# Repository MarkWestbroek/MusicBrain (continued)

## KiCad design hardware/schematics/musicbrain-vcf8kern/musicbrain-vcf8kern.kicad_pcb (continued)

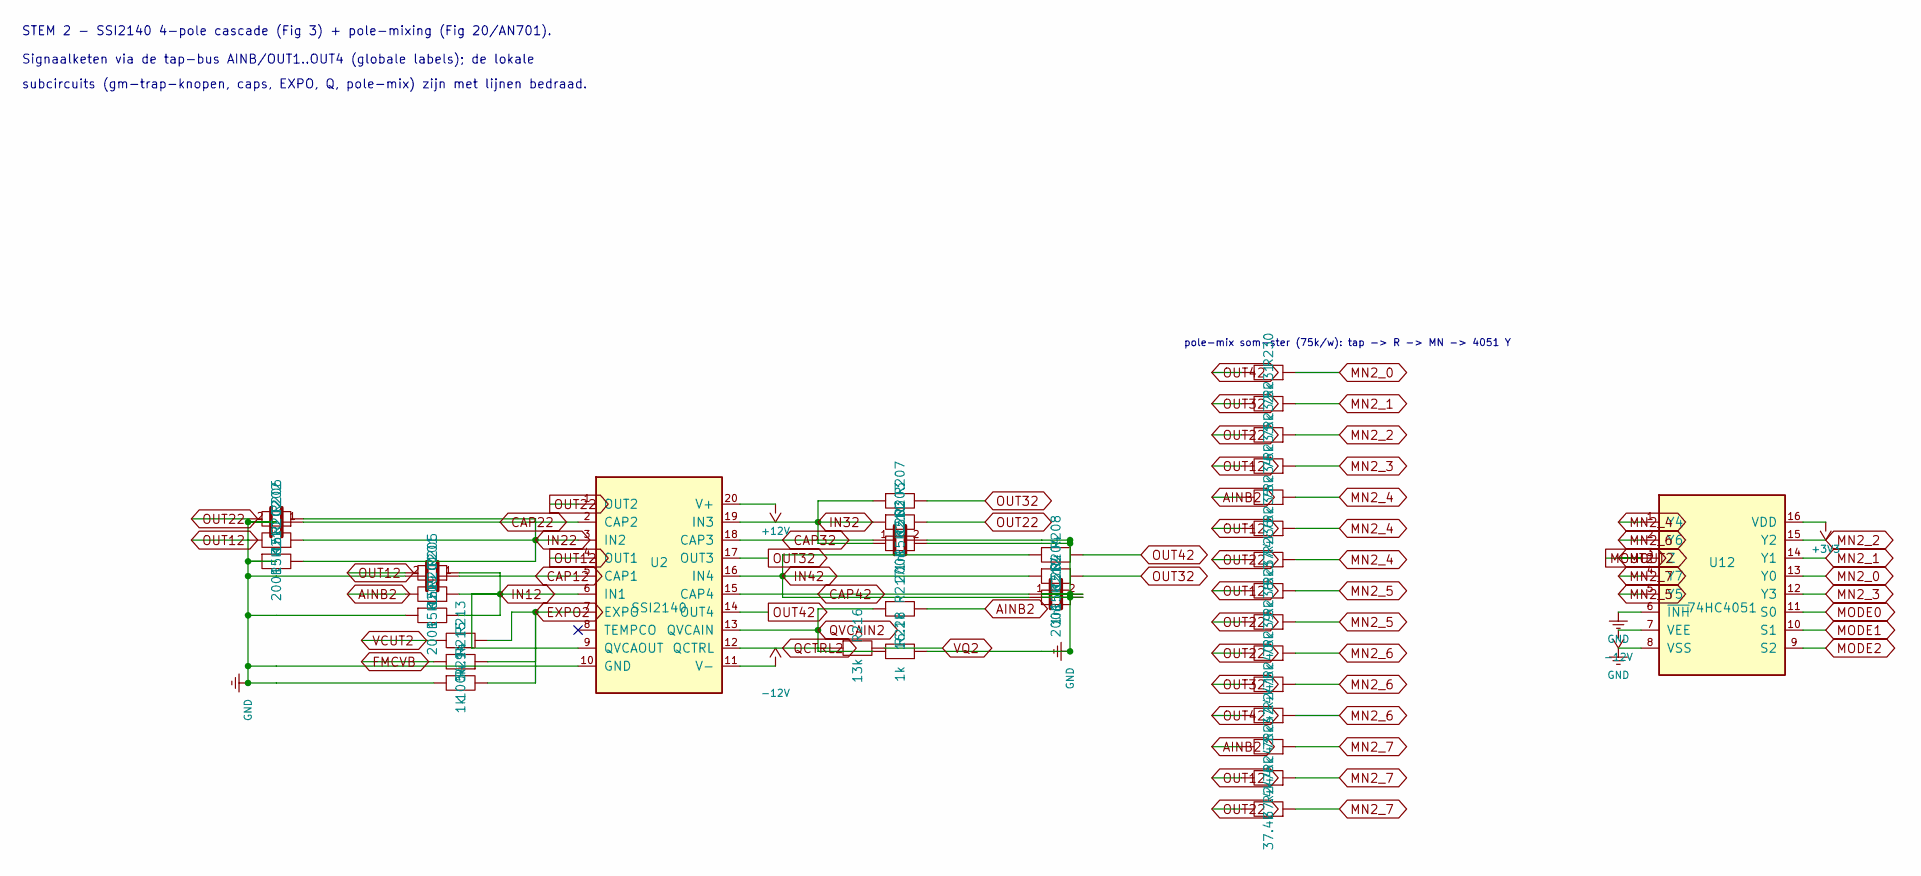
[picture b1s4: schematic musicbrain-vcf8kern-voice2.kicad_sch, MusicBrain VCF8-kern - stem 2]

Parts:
C201, C202, C203, C204: 1n; C_0603_1608Metric
R201, R202, R203, R204, R205, R206, R207, R208: 15k; R_0603_1608Metric
R209, R210, R211, R212: 200R; R_0603_1608Metric
R213: 54.9k; R_0603_1608Metric
R214, R218: 1k; R_0603_1608Metric
R215: 100k; R_0603_1608Metric
R216: 13k; R_0603_1608Metric
R217: 16.2k; R_0603_1608Metric
R230, R231, R232, R233, R234, R236, R237, R238, R239, R241, R242: 75k; R_0603_1608Metric
R235, R240, R243, R244: 37.4k; R_0603_1608Metric
U2: SSI2140; SSOP-20_3.9x8.7mm_P0.635mm
U12: 74HC4051; TSSOP-16_4.4x5mm_P0.65mm

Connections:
+3V3: U12.16 (VDD); also elsewhere on the board
+12V: U2.20 (V+); also elsewhere on the board
-12V: U2.11 (V-), U12.7 (VEE); also elsewhere on the board
AINB2: R201.1, R217.1, R234.1, R242.1; also elsewhere on the board
CAP12: C201.1, U2.5 (CAP1)
CAP22: C202.1, U2.2 (CAP2)
CAP32: C203.1, U2.18 (CAP3)
CAP42: C204.1, U2.15 (CAP4)
EXPO2: R213.2, R214.1, R215.2, U2.7 (EXPO)
FMCVB: R215.1; also elsewhere on the board
GND: C201.2, C202.2, C203.2, C204.2, R209.2, R210.2, R211.2, R212.2, R214.2, R218.2, U2.10 (GND), U12.6 (~INH), U12.8 (VSS); also elsewhere on the board
IN12: R201.2, R205.2, R209.1, U2.6 (IN1), U2.9 (QVCAOUT)
IN22: R202.2, R206.2, R210.1, U2.3 (IN2)
IN32: R203.2, R207.2, R211.1, U2.19 (IN3)
IN42: R204.2, R208.2, R212.1, U2.16 (IN4)
MN2_0: R230.2, U12.13 (Y0)
MN2_1: R231.2, U12.14 (Y1)
MN2_2: R232.2, U12.15 (Y2)
MN2_3: R233.2, U12.12 (Y3)
MN2_4: R234.2, R235.2, R236.2, U12.1 (Y4)
MN2_5: R237.2, R238.2, U12.5 (Y5)
MN2_6: R239.2, R240.2, R241.2, U12.2 (Y6)
MN2_7: R242.2, R243.2, R244.2, U12.4 (Y7)
MODE0: U12.11 (S0); also elsewhere on the board
MODE1: U12.10 (S1); also elsewhere on the board
MODE2: U12.9 (S2); also elsewhere on the board
MOUT2: U12.3 (Z); also elsewhere on the board
OUT12: R202.1, R205.1, R233.1, R235.1, R237.1, R243.1, U2.4 (OUT1)
OUT22: R203.1, R206.1, R232.1, R236.1, R238.1, R239.1, R244.1, U2.1 (OUT2)
OUT32: R204.1, R207.1, R231.1, R240.1, U2.17 (OUT3)
OUT42: R208.1, R230.1, R241.1, U2.14 (OUT4); also elsewhere on the board
QCTRL2: R216.2, U2.12 (QCTRL)
QVCAIN2: R217.2, R218.1, U2.13 (QVCAIN)
VCUT2: R213.1; also elsewhere on the board
VQ2: R216.1; also elsewhere on the board

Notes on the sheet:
pole-mix som-ster (75k/w): tap -> R -> MN -> 4051 Y
STEM 2 - SSI2140 4-pole cascade (Fig 3) + pole-mixing (Fig 20/AN701).
Signaalketen via de tap-bus AINB/OUT1..OUT4 (globale labels); de lokale
subcircuits (gm-trap-knopen, caps, EXPO, Q, pole-mix) zijn met lijnen bedraad.

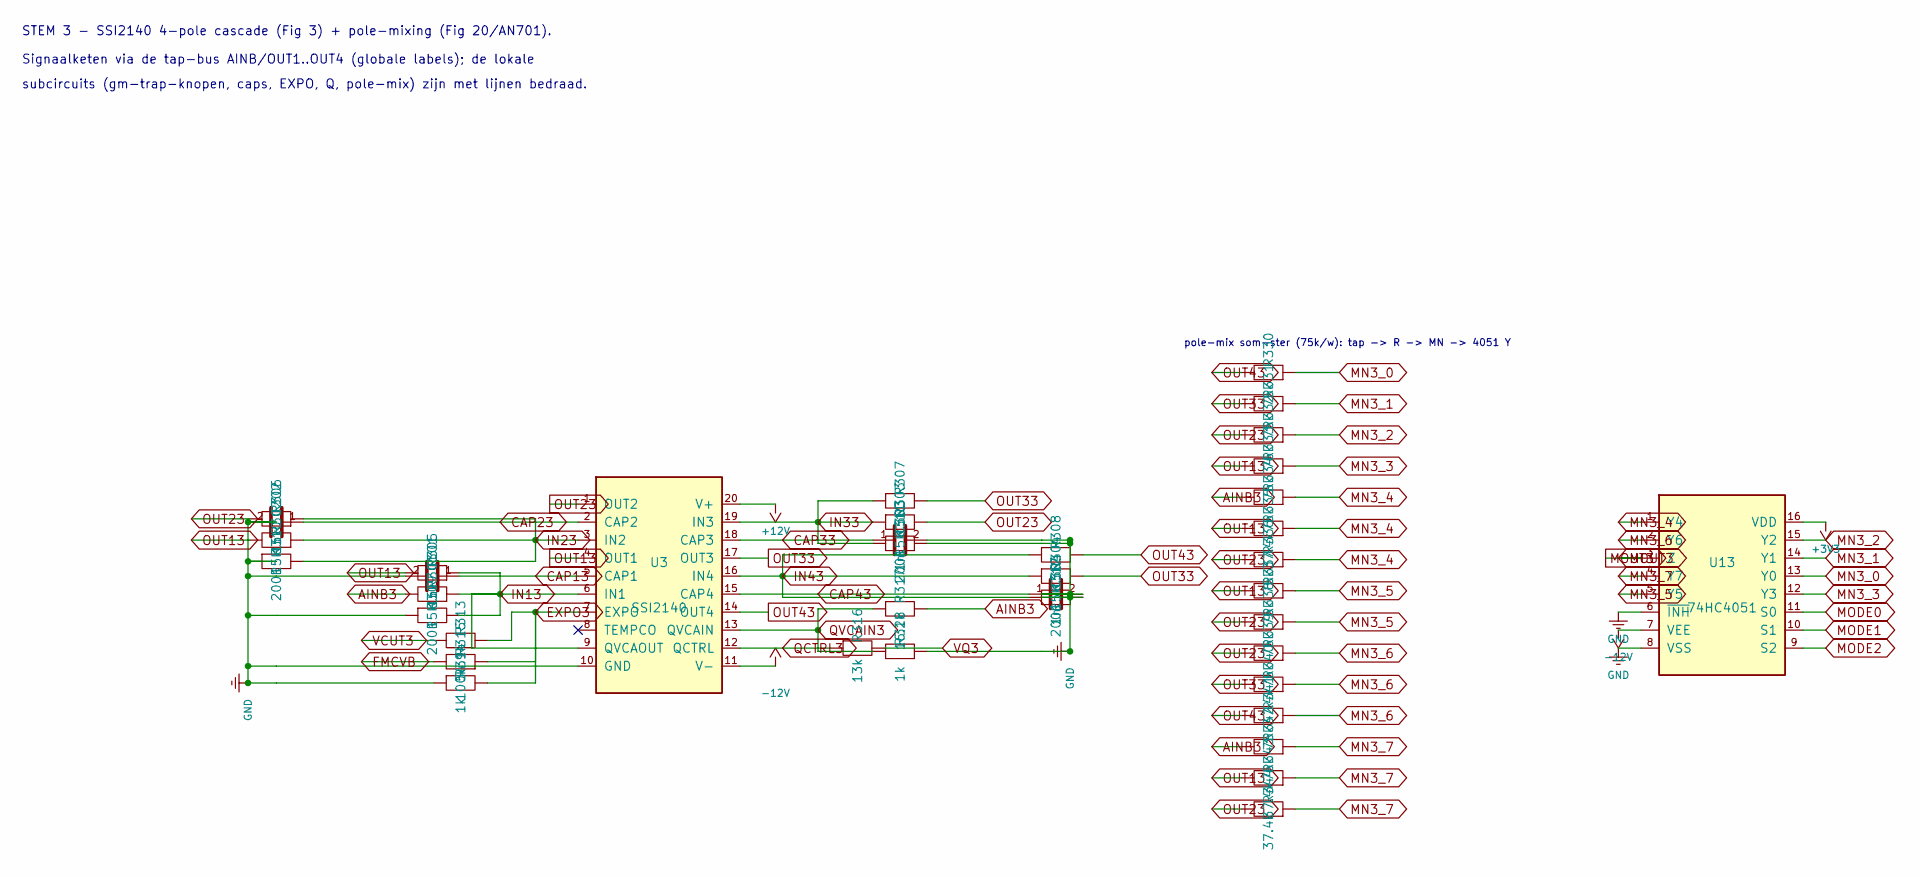
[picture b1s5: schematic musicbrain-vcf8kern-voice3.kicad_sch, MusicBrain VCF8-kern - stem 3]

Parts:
C301, C302, C303, C304: 1n; C_0603_1608Metric
R301, R302, R303, R304, R305, R306, R307, R308: 15k; R_0603_1608Metric
R309, R310, R311, R312: 200R; R_0603_1608Metric
R313: 54.9k; R_0603_1608Metric
R314, R318: 1k; R_0603_1608Metric
R315: 100k; R_0603_1608Metric
R316: 13k; R_0603_1608Metric
R317: 16.2k; R_0603_1608Metric
R330, R331, R332, R333, R334, R336, R337, R338, R339, R341, R342: 75k; R_0603_1608Metric
R335, R340, R343, R344: 37.4k; R_0603_1608Metric
U3: SSI2140; SSOP-20_3.9x8.7mm_P0.635mm
U13: 74HC4051; TSSOP-16_4.4x5mm_P0.65mm

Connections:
+3V3: U13.16 (VDD); also elsewhere on the board
+12V: U3.20 (V+); also elsewhere on the board
-12V: U3.11 (V-), U13.7 (VEE); also elsewhere on the board
AINB3: R301.1, R317.1, R334.1, R342.1; also elsewhere on the board
CAP13: C301.1, U3.5 (CAP1)
CAP23: C302.1, U3.2 (CAP2)
CAP33: C303.1, U3.18 (CAP3)
CAP43: C304.1, U3.15 (CAP4)
EXPO3: R313.2, R314.1, R315.2, U3.7 (EXPO)
FMCVB: R315.1; also elsewhere on the board
GND: C301.2, C302.2, C303.2, C304.2, R309.2, R310.2, R311.2, R312.2, R314.2, R318.2, U3.10 (GND), U13.6 (~INH), U13.8 (VSS); also elsewhere on the board
IN13: R301.2, R305.2, R309.1, U3.6 (IN1), U3.9 (QVCAOUT)
IN23: R302.2, R306.2, R310.1, U3.3 (IN2)
IN33: R303.2, R307.2, R311.1, U3.19 (IN3)
IN43: R304.2, R308.2, R312.1, U3.16 (IN4)
MN3_0: R330.2, U13.13 (Y0)
MN3_1: R331.2, U13.14 (Y1)
MN3_2: R332.2, U13.15 (Y2)
MN3_3: R333.2, U13.12 (Y3)
MN3_4: R334.2, R335.2, R336.2, U13.1 (Y4)
MN3_5: R337.2, R338.2, U13.5 (Y5)
MN3_6: R339.2, R340.2, R341.2, U13.2 (Y6)
MN3_7: R342.2, R343.2, R344.2, U13.4 (Y7)
MODE0: U13.11 (S0); also elsewhere on the board
MODE1: U13.10 (S1); also elsewhere on the board
MODE2: U13.9 (S2); also elsewhere on the board
MOUT3: U13.3 (Z); also elsewhere on the board
OUT13: R302.1, R305.1, R333.1, R335.1, R337.1, R343.1, U3.4 (OUT1)
OUT23: R303.1, R306.1, R332.1, R336.1, R338.1, R339.1, R344.1, U3.1 (OUT2)
OUT33: R304.1, R307.1, R331.1, R340.1, U3.17 (OUT3)
OUT43: R308.1, R330.1, R341.1, U3.14 (OUT4); also elsewhere on the board
QCTRL3: R316.2, U3.12 (QCTRL)
QVCAIN3: R317.2, R318.1, U3.13 (QVCAIN)
VCUT3: R313.1; also elsewhere on the board
VQ3: R316.1; also elsewhere on the board

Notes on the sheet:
pole-mix som-ster (75k/w): tap -> R -> MN -> 4051 Y
STEM 3 - SSI2140 4-pole cascade (Fig 3) + pole-mixing (Fig 20/AN701).
Signaalketen via de tap-bus AINB/OUT1..OUT4 (globale labels); de lokale
subcircuits (gm-trap-knopen, caps, EXPO, Q, pole-mix) zijn met lijnen bedraad.

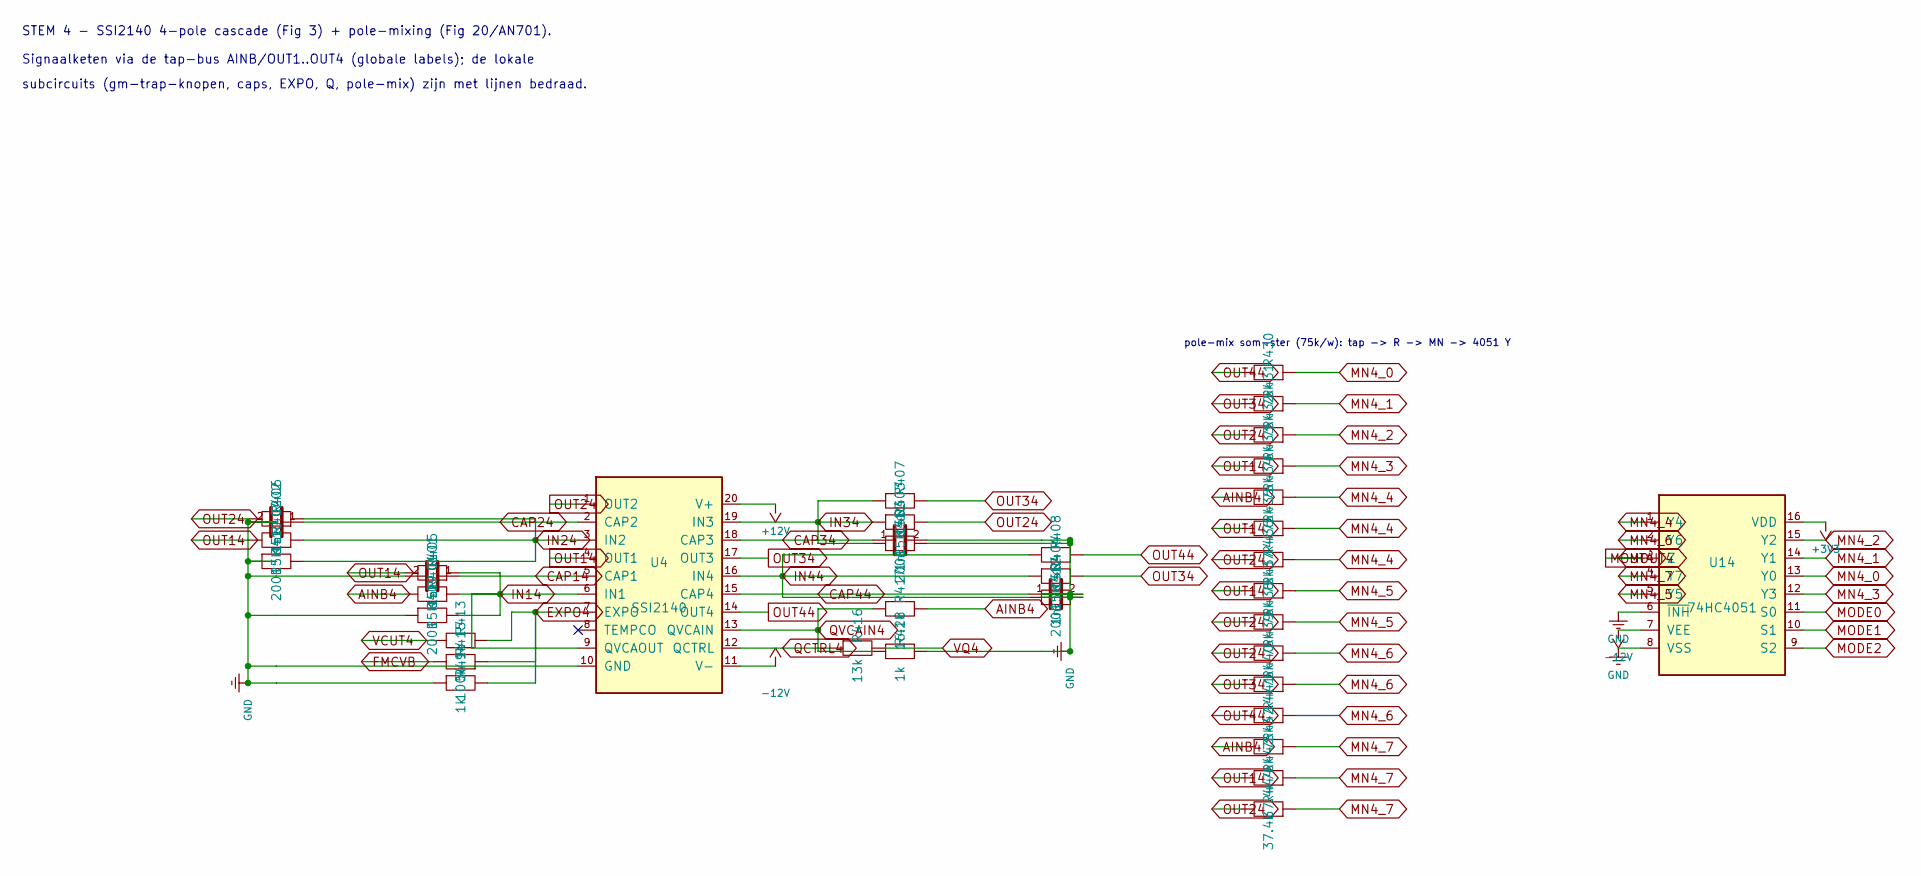
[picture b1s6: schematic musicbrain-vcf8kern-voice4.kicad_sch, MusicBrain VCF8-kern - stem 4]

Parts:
C401, C402, C403, C404: 1n; C_0603_1608Metric
R401, R402, R403, R404, R405, R406, R407, R408: 15k; R_0603_1608Metric
R409, R410, R411, R412: 200R; R_0603_1608Metric
R413: 54.9k; R_0603_1608Metric
R414, R418: 1k; R_0603_1608Metric
R415: 100k; R_0603_1608Metric
R416: 13k; R_0603_1608Metric
R417: 16.2k; R_0603_1608Metric
R430, R431, R432, R433, R434, R436, R437, R438, R439, R441, R442: 75k; R_0603_1608Metric
R435, R440, R443, R444: 37.4k; R_0603_1608Metric
U4: SSI2140; SSOP-20_3.9x8.7mm_P0.635mm
U14: 74HC4051; TSSOP-16_4.4x5mm_P0.65mm

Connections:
+3V3: U14.16 (VDD); also elsewhere on the board
+12V: U4.20 (V+); also elsewhere on the board
-12V: U4.11 (V-), U14.7 (VEE); also elsewhere on the board
AINB4: R401.1, R417.1, R434.1, R442.1; also elsewhere on the board
CAP14: C401.1, U4.5 (CAP1)
CAP24: C402.1, U4.2 (CAP2)
CAP34: C403.1, U4.18 (CAP3)
CAP44: C404.1, U4.15 (CAP4)
EXPO4: R413.2, R414.1, R415.2, U4.7 (EXPO)
FMCVB: R415.1; also elsewhere on the board
GND: C401.2, C402.2, C403.2, C404.2, R409.2, R410.2, R411.2, R412.2, R414.2, R418.2, U4.10 (GND), U14.6 (~INH), U14.8 (VSS); also elsewhere on the board
IN14: R401.2, R405.2, R409.1, U4.6 (IN1), U4.9 (QVCAOUT)
IN24: R402.2, R406.2, R410.1, U4.3 (IN2)
IN34: R403.2, R407.2, R411.1, U4.19 (IN3)
IN44: R404.2, R408.2, R412.1, U4.16 (IN4)
MN4_0: R430.2, U14.13 (Y0)
MN4_1: R431.2, U14.14 (Y1)
MN4_2: R432.2, U14.15 (Y2)
MN4_3: R433.2, U14.12 (Y3)
MN4_4: R434.2, R435.2, R436.2, U14.1 (Y4)
MN4_5: R437.2, R438.2, U14.5 (Y5)
MN4_6: R439.2, R440.2, R441.2, U14.2 (Y6)
MN4_7: R442.2, R443.2, R444.2, U14.4 (Y7)
MODE0: U14.11 (S0); also elsewhere on the board
MODE1: U14.10 (S1); also elsewhere on the board
MODE2: U14.9 (S2); also elsewhere on the board
MOUT4: U14.3 (Z); also elsewhere on the board
OUT14: R402.1, R405.1, R433.1, R435.1, R437.1, R443.1, U4.4 (OUT1)
OUT24: R403.1, R406.1, R432.1, R436.1, R438.1, R439.1, R444.1, U4.1 (OUT2)
OUT34: R404.1, R407.1, R431.1, R440.1, U4.17 (OUT3)
OUT44: R408.1, R430.1, R441.1, U4.14 (OUT4); also elsewhere on the board
QCTRL4: R416.2, U4.12 (QCTRL)
QVCAIN4: R417.2, R418.1, U4.13 (QVCAIN)
VCUT4: R413.1; also elsewhere on the board
VQ4: R416.1; also elsewhere on the board

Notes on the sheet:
pole-mix som-ster (75k/w): tap -> R -> MN -> 4051 Y
STEM 4 - SSI2140 4-pole cascade (Fig 3) + pole-mixing (Fig 20/AN701).
Signaalketen via de tap-bus AINB/OUT1..OUT4 (globale labels); de lokale
subcircuits (gm-trap-knopen, caps, EXPO, Q, pole-mix) zijn met lijnen bedraad.

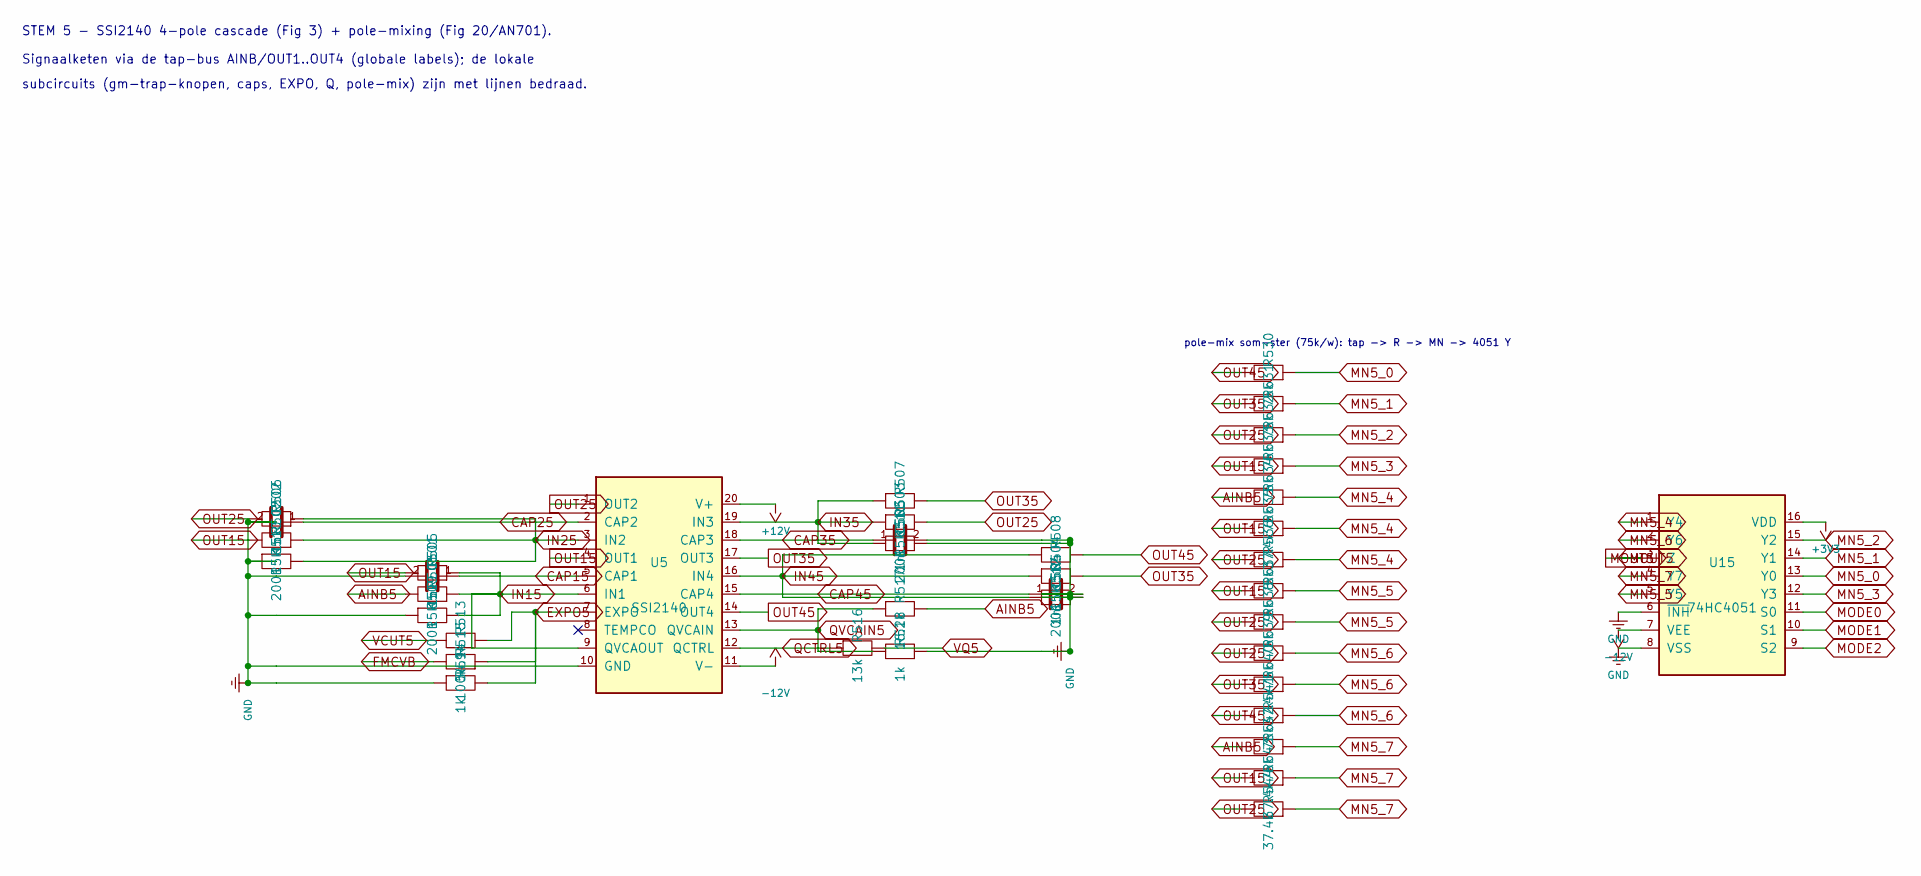
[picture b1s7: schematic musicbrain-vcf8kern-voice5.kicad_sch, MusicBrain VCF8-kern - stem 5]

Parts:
C501, C502, C503, C504: 1n; C_0603_1608Metric
R501, R502, R503, R504, R505, R506, R507, R508: 15k; R_0603_1608Metric
R509, R510, R511, R512: 200R; R_0603_1608Metric
R513: 54.9k; R_0603_1608Metric
R514, R518: 1k; R_0603_1608Metric
R515: 100k; R_0603_1608Metric
R516: 13k; R_0603_1608Metric
R517: 16.2k; R_0603_1608Metric
R530, R531, R532, R533, R534, R536, R537, R538, R539, R541, R542: 75k; R_0603_1608Metric
R535, R540, R543, R544: 37.4k; R_0603_1608Metric
U5: SSI2140; SSOP-20_3.9x8.7mm_P0.635mm
U15: 74HC4051; TSSOP-16_4.4x5mm_P0.65mm

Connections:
+3V3: U15.16 (VDD); also elsewhere on the board
+12V: U5.20 (V+); also elsewhere on the board
-12V: U5.11 (V-), U15.7 (VEE); also elsewhere on the board
AINB5: R501.1, R517.1, R534.1, R542.1; also elsewhere on the board
CAP15: C501.1, U5.5 (CAP1)
CAP25: C502.1, U5.2 (CAP2)
CAP35: C503.1, U5.18 (CAP3)
CAP45: C504.1, U5.15 (CAP4)
EXPO5: R513.2, R514.1, R515.2, U5.7 (EXPO)
FMCVB: R515.1; also elsewhere on the board
GND: C501.2, C502.2, C503.2, C504.2, R509.2, R510.2, R511.2, R512.2, R514.2, R518.2, U5.10 (GND), U15.6 (~INH), U15.8 (VSS); also elsewhere on the board
IN15: R501.2, R505.2, R509.1, U5.6 (IN1), U5.9 (QVCAOUT)
IN25: R502.2, R506.2, R510.1, U5.3 (IN2)
IN35: R503.2, R507.2, R511.1, U5.19 (IN3)
IN45: R504.2, R508.2, R512.1, U5.16 (IN4)
MN5_0: R530.2, U15.13 (Y0)
MN5_1: R531.2, U15.14 (Y1)
MN5_2: R532.2, U15.15 (Y2)
MN5_3: R533.2, U15.12 (Y3)
MN5_4: R534.2, R535.2, R536.2, U15.1 (Y4)
MN5_5: R537.2, R538.2, U15.5 (Y5)
MN5_6: R539.2, R540.2, R541.2, U15.2 (Y6)
MN5_7: R542.2, R543.2, R544.2, U15.4 (Y7)
MODE0: U15.11 (S0); also elsewhere on the board
MODE1: U15.10 (S1); also elsewhere on the board
MODE2: U15.9 (S2); also elsewhere on the board
MOUT5: U15.3 (Z); also elsewhere on the board
OUT15: R502.1, R505.1, R533.1, R535.1, R537.1, R543.1, U5.4 (OUT1)
OUT25: R503.1, R506.1, R532.1, R536.1, R538.1, R539.1, R544.1, U5.1 (OUT2)
OUT35: R504.1, R507.1, R531.1, R540.1, U5.17 (OUT3)
OUT45: R508.1, R530.1, R541.1, U5.14 (OUT4); also elsewhere on the board
QCTRL5: R516.2, U5.12 (QCTRL)
QVCAIN5: R517.2, R518.1, U5.13 (QVCAIN)
VCUT5: R513.1; also elsewhere on the board
VQ5: R516.1; also elsewhere on the board

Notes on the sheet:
pole-mix som-ster (75k/w): tap -> R -> MN -> 4051 Y
STEM 5 - SSI2140 4-pole cascade (Fig 3) + pole-mixing (Fig 20/AN701).
Signaalketen via de tap-bus AINB/OUT1..OUT4 (globale labels); de lokale
subcircuits (gm-trap-knopen, caps, EXPO, Q, pole-mix) zijn met lijnen bedraad.

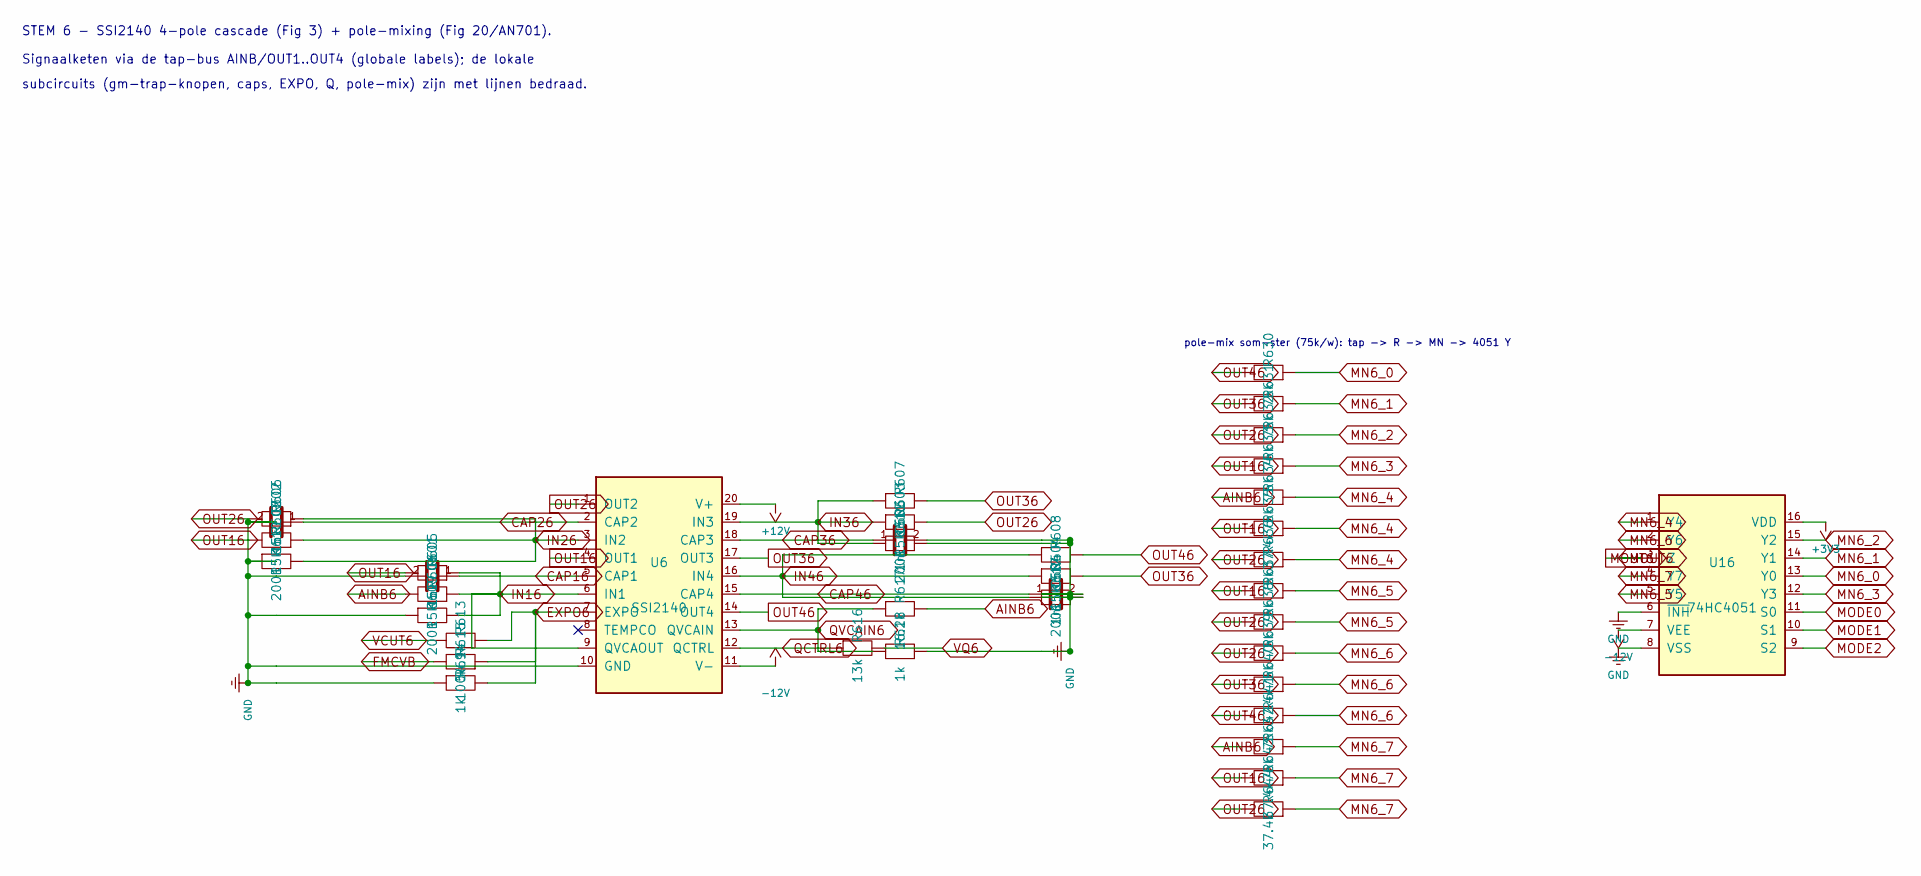
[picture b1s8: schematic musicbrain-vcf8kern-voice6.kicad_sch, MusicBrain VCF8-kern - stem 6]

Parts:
C601, C602, C603, C604: 1n; C_0603_1608Metric
R601, R602, R603, R604, R605, R606, R607, R608: 15k; R_0603_1608Metric
R609, R610, R611, R612: 200R; R_0603_1608Metric
R613: 54.9k; R_0603_1608Metric
R614, R618: 1k; R_0603_1608Metric
R615: 100k; R_0603_1608Metric
R616: 13k; R_0603_1608Metric
R617: 16.2k; R_0603_1608Metric
R630, R631, R632, R633, R634, R636, R637, R638, R639, R641, R642: 75k; R_0603_1608Metric
R635, R640, R643, R644: 37.4k; R_0603_1608Metric
U6: SSI2140; SSOP-20_3.9x8.7mm_P0.635mm
U16: 74HC4051; TSSOP-16_4.4x5mm_P0.65mm

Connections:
+3V3: U16.16 (VDD); also elsewhere on the board
+12V: U6.20 (V+); also elsewhere on the board
-12V: U6.11 (V-), U16.7 (VEE); also elsewhere on the board
AINB6: R601.1, R617.1, R634.1, R642.1; also elsewhere on the board
CAP16: C601.1, U6.5 (CAP1)
CAP26: C602.1, U6.2 (CAP2)
CAP36: C603.1, U6.18 (CAP3)
CAP46: C604.1, U6.15 (CAP4)
EXPO6: R613.2, R614.1, R615.2, U6.7 (EXPO)
FMCVB: R615.1; also elsewhere on the board
GND: C601.2, C602.2, C603.2, C604.2, R609.2, R610.2, R611.2, R612.2, R614.2, R618.2, U6.10 (GND), U16.6 (~INH), U16.8 (VSS); also elsewhere on the board
IN16: R601.2, R605.2, R609.1, U6.6 (IN1), U6.9 (QVCAOUT)
IN26: R602.2, R606.2, R610.1, U6.3 (IN2)
IN36: R603.2, R607.2, R611.1, U6.19 (IN3)
IN46: R604.2, R608.2, R612.1, U6.16 (IN4)
MN6_0: R630.2, U16.13 (Y0)
MN6_1: R631.2, U16.14 (Y1)
MN6_2: R632.2, U16.15 (Y2)
MN6_3: R633.2, U16.12 (Y3)
MN6_4: R634.2, R635.2, R636.2, U16.1 (Y4)
MN6_5: R637.2, R638.2, U16.5 (Y5)
MN6_6: R639.2, R640.2, R641.2, U16.2 (Y6)
MN6_7: R642.2, R643.2, R644.2, U16.4 (Y7)
MODE0: U16.11 (S0); also elsewhere on the board
MODE1: U16.10 (S1); also elsewhere on the board
MODE2: U16.9 (S2); also elsewhere on the board
MOUT6: U16.3 (Z); also elsewhere on the board
OUT16: R602.1, R605.1, R633.1, R635.1, R637.1, R643.1, U6.4 (OUT1)
OUT26: R603.1, R606.1, R632.1, R636.1, R638.1, R639.1, R644.1, U6.1 (OUT2)
OUT36: R604.1, R607.1, R631.1, R640.1, U6.17 (OUT3)
OUT46: R608.1, R630.1, R641.1, U6.14 (OUT4); also elsewhere on the board
QCTRL6: R616.2, U6.12 (QCTRL)
QVCAIN6: R617.2, R618.1, U6.13 (QVCAIN)
VCUT6: R613.1; also elsewhere on the board
VQ6: R616.1; also elsewhere on the board

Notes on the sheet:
pole-mix som-ster (75k/w): tap -> R -> MN -> 4051 Y
STEM 6 - SSI2140 4-pole cascade (Fig 3) + pole-mixing (Fig 20/AN701).
Signaalketen via de tap-bus AINB/OUT1..OUT4 (globale labels); de lokale
subcircuits (gm-trap-knopen, caps, EXPO, Q, pole-mix) zijn met lijnen bedraad.

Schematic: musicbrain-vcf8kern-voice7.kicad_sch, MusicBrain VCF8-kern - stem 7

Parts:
C701, C702, C703, C704: 1n; C_0603_1608Metric
R701, R702, R703, R704, R705, R706, R707, R708: 15k; R_0603_1608Metric
R709, R710, R711, R712: 200R; R_0603_1608Metric
R713: 54.9k; R_0603_1608Metric
R714, R718: 1k; R_0603_1608Metric
R715: 100k; R_0603_1608Metric
R716: 13k; R_0603_1608Metric
R717: 16.2k; R_0603_1608Metric
R730, R731, R732, R733, R734, R736, R737, R738, R739, R741, R742: 75k; R_0603_1608Metric
R735, R740, R743, R744: 37.4k; R_0603_1608Metric
U7: SSI2140; SSOP-20_3.9x8.7mm_P0.635mm
U17: 74HC4051; TSSOP-16_4.4x5mm_P0.65mm

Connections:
+3V3: U17.16 (VDD); also elsewhere on the board
+12V: U7.20 (V+); also elsewhere on the board
-12V: U7.11 (V-), U17.7 (VEE); also elsewhere on the board
AINB7: R701.1, R717.1, R734.1, R742.1; also elsewhere on the board
CAP17: C701.1, U7.5 (CAP1)
CAP27: C702.1, U7.2 (CAP2)
CAP37: C703.1, U7.18 (CAP3)
CAP47: C704.1, U7.15 (CAP4)
EXPO7: R713.2, R714.1, R715.2, U7.7 (EXPO)
FMCVB: R715.1; also elsewhere on the board
GND: C701.2, C702.2, C703.2, C704.2, R709.2, R710.2, R711.2, R712.2, R714.2, R718.2, U7.10 (GND), U17.6 (~INH), U17.8 (VSS); also elsewhere on the board
IN17: R701.2, R705.2, R709.1, U7.6 (IN1), U7.9 (QVCAOUT)
IN27: R702.2, R706.2, R710.1, U7.3 (IN2)
IN37: R703.2, R707.2, R711.1, U7.19 (IN3)
IN47: R704.2, R708.2, R712.1, U7.16 (IN4)
MN7_0: R730.2, U17.13 (Y0)
MN7_1: R731.2, U17.14 (Y1)
MN7_2: R732.2, U17.15 (Y2)
MN7_3: R733.2, U17.12 (Y3)
MN7_4: R734.2, R735.2, R736.2, U17.1 (Y4)
MN7_5: R737.2, R738.2, U17.5 (Y5)
MN7_6: R739.2, R740.2, R741.2, U17.2 (Y6)
MN7_7: R742.2, R743.2, R744.2, U17.4 (Y7)
MODE0: U17.11 (S0); also elsewhere on the board
MODE1: U17.10 (S1); also elsewhere on the board
MODE2: U17.9 (S2); also elsewhere on the board
MOUT7: U17.3 (Z); also elsewhere on the board
OUT17: R702.1, R705.1, R733.1, R735.1, R737.1, R743.1, U7.4 (OUT1)
OUT27: R703.1, R706.1, R732.1, R736.1, R738.1, R739.1, R744.1, U7.1 (OUT2)
OUT37: R704.1, R707.1, R731.1, R740.1, U7.17 (OUT3)
OUT47: R708.1, R730.1, R741.1, U7.14 (OUT4); also elsewhere on the board
QCTRL7: R716.2, U7.12 (QCTRL)
QVCAIN7: R717.2, R718.1, U7.13 (QVCAIN)
VCUT7: R713.1; also elsewhere on the board
VQ7: R716.1; also elsewhere on the board

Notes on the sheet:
pole-mix som-ster (75k/w): tap -> R -> MN -> 4051 Y
STEM 7 - SSI2140 4-pole cascade (Fig 3) + pole-mixing (Fig 20/AN701).
Signaalketen via de tap-bus AINB/OUT1..OUT4 (globale labels); de lokale
subcircuits (gm-trap-knopen, caps, EXPO, Q, pole-mix) zijn met lijnen bedraad.

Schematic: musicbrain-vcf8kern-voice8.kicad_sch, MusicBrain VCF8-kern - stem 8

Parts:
C801, C802, C803, C804: 1n; C_0603_1608Metric
R801, R802, R803, R804, R805, R806, R807, R808: 15k; R_0603_1608Metric
R809, R810, R811, R812: 200R; R_0603_1608Metric
R813: 54.9k; R_0603_1608Metric
R814, R818: 1k; R_0603_1608Metric
R815: 100k; R_0603_1608Metric
R816: 13k; R_0603_1608Metric
R817: 16.2k; R_0603_1608Metric
R830, R831, R832, R833, R834, R836, R837, R838, R839, R841, R842: 75k; R_0603_1608Metric
R835, R840, R843, R844: 37.4k; R_0603_1608Metric
U8: SSI2140; SSOP-20_3.9x8.7mm_P0.635mm
U18: 74HC4051; TSSOP-16_4.4x5mm_P0.65mm

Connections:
+3V3: U18.16 (VDD); also elsewhere on the board
+12V: U8.20 (V+); also elsewhere on the board
-12V: U8.11 (V-), U18.7 (VEE); also elsewhere on the board
AINB8: R801.1, R817.1, R834.1, R842.1; also elsewhere on the board
CAP18: C801.1, U8.5 (CAP1)
CAP28: C802.1, U8.2 (CAP2)
CAP38: C803.1, U8.18 (CAP3)
CAP48: C804.1, U8.15 (CAP4)
EXPO8: R813.2, R814.1, R815.2, U8.7 (EXPO)
FMCVB: R815.1; also elsewhere on the board
GND: C801.2, C802.2, C803.2, C804.2, R809.2, R810.2, R811.2, R812.2, R814.2, R818.2, U8.10 (GND), U18.6 (~INH), U18.8 (VSS); also elsewhere on the board
IN18: R801.2, R805.2, R809.1, U8.6 (IN1), U8.9 (QVCAOUT)
IN28: R802.2, R806.2, R810.1, U8.3 (IN2)
IN38: R803.2, R807.2, R811.1, U8.19 (IN3)
IN48: R804.2, R808.2, R812.1, U8.16 (IN4)
MN8_0: R830.2, U18.13 (Y0)
MN8_1: R831.2, U18.14 (Y1)
MN8_2: R832.2, U18.15 (Y2)
MN8_3: R833.2, U18.12 (Y3)
MN8_4: R834.2, R835.2, R836.2, U18.1 (Y4)
MN8_5: R837.2, R838.2, U18.5 (Y5)
MN8_6: R839.2, R840.2, R841.2, U18.2 (Y6)
MN8_7: R842.2, R843.2, R844.2, U18.4 (Y7)
MODE0: U18.11 (S0); also elsewhere on the board
MODE1: U18.10 (S1); also elsewhere on the board
MODE2: U18.9 (S2); also elsewhere on the board
MOUT8: U18.3 (Z); also elsewhere on the board
OUT18: R802.1, R805.1, R833.1, R835.1, R837.1, R843.1, U8.4 (OUT1)
OUT28: R803.1, R806.1, R832.1, R836.1, R838.1, R839.1, R844.1, U8.1 (OUT2)
OUT38: R804.1, R807.1, R831.1, R840.1, U8.17 (OUT3)
OUT48: R808.1, R830.1, R841.1, U8.14 (OUT4); also elsewhere on the board
QCTRL8: R816.2, U8.12 (QCTRL)
QVCAIN8: R817.2, R818.1, U8.13 (QVCAIN)
VCUT8: R813.1; also elsewhere on the board
VQ8: R816.1; also elsewhere on the board

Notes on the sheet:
pole-mix som-ster (75k/w): tap -> R -> MN -> 4051 Y
STEM 8 - SSI2140 4-pole cascade (Fig 3) + pole-mixing (Fig 20/AN701).
Signaalketen via de tap-bus AINB/OUT1..OUT4 (globale labels); de lokale
subcircuits (gm-trap-knopen, caps, EXPO, Q, pole-mix) zijn met lijnen bedraad.
